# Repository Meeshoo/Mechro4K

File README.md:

# Mechro 4K
An AtmegaA32U4 powered 4 key mechanical macro pad with custom PCB made in KiCad running QMK firmware.

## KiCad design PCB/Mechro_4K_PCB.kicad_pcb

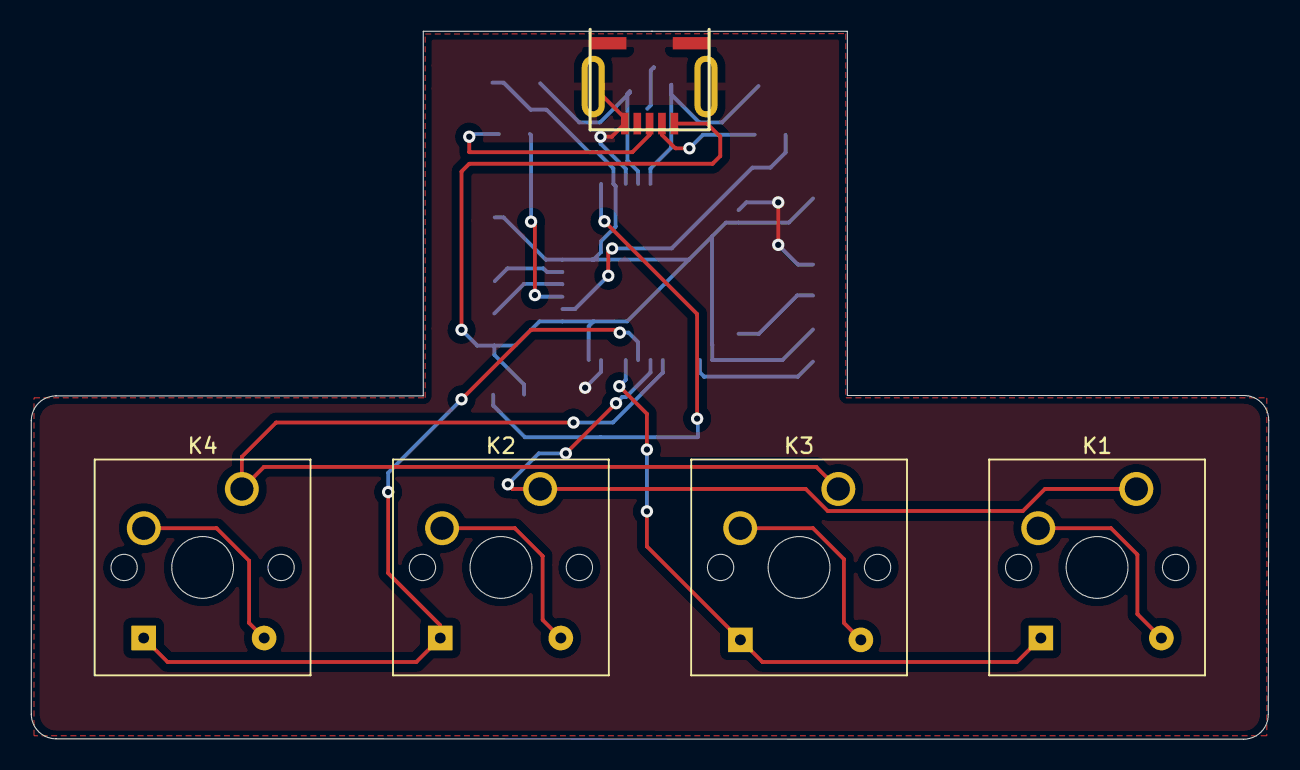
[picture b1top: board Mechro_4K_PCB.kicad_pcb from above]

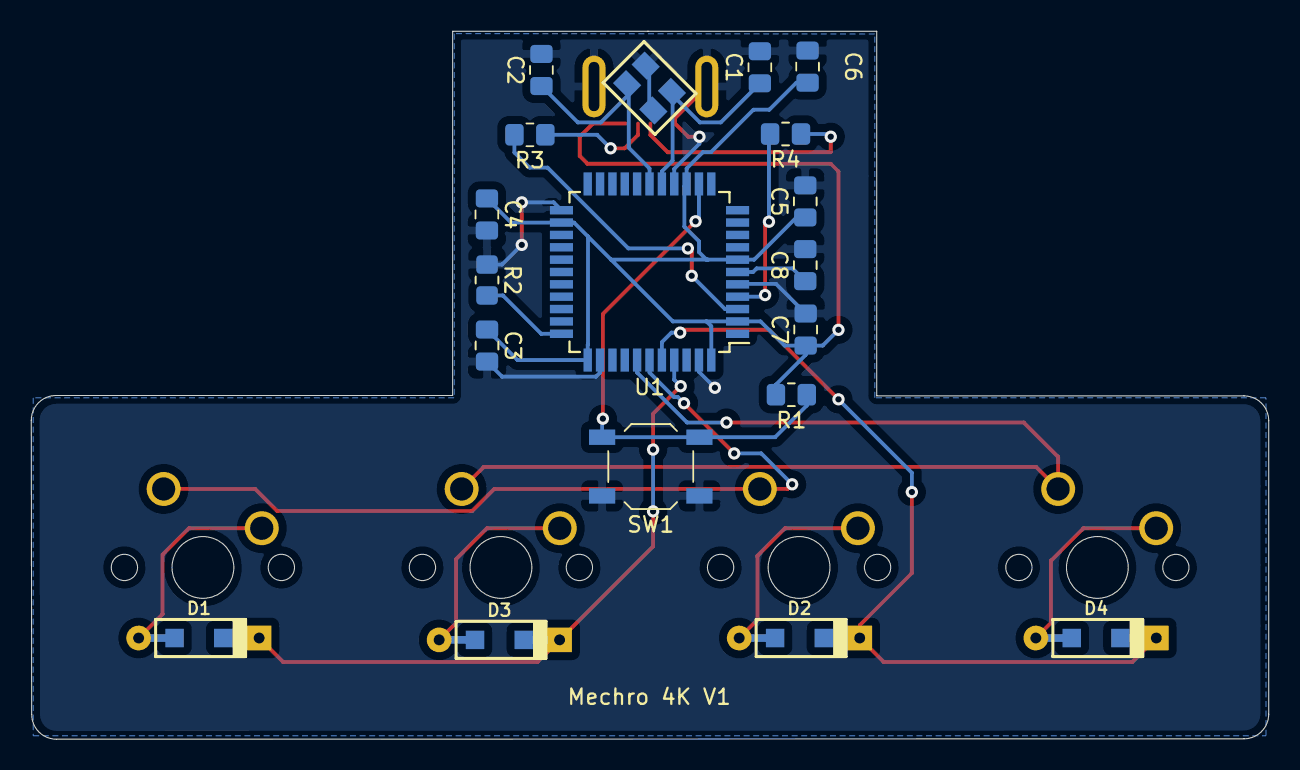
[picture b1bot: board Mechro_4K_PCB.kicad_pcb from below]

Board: 2 copper layers, 80.1 x 45.8 mm, 24 parts (19 on the bottom side), 19 nets.

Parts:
C1, C2: 22p; C_0805_2012Metric_Pad1.18x1.45mm_HandSolder
C3, C4, C5, C6: 0.1u; C_0805_2012Metric_Pad1.18x1.45mm_HandSolder
C7: 4.7u; C_0805_2012Metric_Pad1.18x1.45mm_HandSolder
C8: 1u; C_0805_2012Metric_Pad1.18x1.45mm_HandSolder
D1, D2, D3, D4: D; D_SOD123_axial
J1: USB_mini_micro_B; USB_miniB_hirose_5S8
K1, K2, K3, K4: KEYSW; SW_Cherry_MX_1.00u_PCB
R1, R2: 10K; R_0805_2012Metric_Pad1.20x1.40mm_HandSolder
R3, R4: 22; R_0805_2012Metric_Pad1.20x1.40mm_HandSolder
SW1: SW_PUSH; SW_SPST_TL3342
U1: ATMEGA32U4; TQFP-44_10x10mm_P0.8mm
X1: XTAL_GND; FA-238

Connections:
/col0: K1.1, K2.1, U1.39
/col1: K3.1, K4.1, U1.38
/row0: D1.1, D3.1, U1.41
/row1: D2.1, D4.1, U1.40
GND: C1.2, C2.2, C3.2, C4.2, C5.2, C6.2, C7.2, C8.2, J1.5, J1.6, R2.1, SW1.1, U1.5, U1.15, U1.23, U1.35, U1.43, X1.3
unnamed: C1.1, U1.16, X1.1
unnamed: C2.1, U1.17, X1.2
unnamed: C8.1, U1.6
unnamed: D1.2, K1.2
unnamed: D2.2, K2.2
unnamed: D3.2, K3.2
unnamed: D4.2, K4.2
unnamed: J1.2, R3.1
unnamed: J1.3, R4.1
unnamed: R1.1, SW1.2, U1.13
unnamed: R2.2, U1.33
unnamed: R3.2, U1.3
unnamed: R4.2, U1.4
VCC: C3.1, C4.1, C5.1, C6.1, C7.1, J1.1, R1.2, U1.2, U1.7, U1.14, U1.24, U1.34, U1.44
